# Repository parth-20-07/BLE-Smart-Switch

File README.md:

<!-- omit from toc -->
# BLE Smart Switch

**Table of Contents**

- [Why BLE Smart Switch is needed?](#why-ble-smart-switch-is-needed)
- [Features of our Smart Switch](#features-of-our-smart-switch)
- [How to use the device](#how-to-use-the-device)
- [Schematic Design](#schematic-design)
- [PCB Design](#pcb-design)
- [Rendered Images](#rendered-images)
- [Design Details](#design-details)

# Why BLE Smart Switch is needed?

The BLE Smart Switch provides convenient control over electrical sockets through Bluetooth technology. It enables users to manage home appliances remotely, ensuring energy efficiency and enhanced home automation.

# Features of our Smart Switch

- Control up to 2 sockets remotely.
- Schedule socket activation/deactivation.
- Real-time monitoring and control through a BLE app.
- Easy-to-use interface for hassle-free operation.
- Compact and modern design, suitable for various environments.

# How to use the device

1. Connect the device to the sockets you wish to control.
2. Pair the device with the BLE app.
3. Use the app to set schedules or control sockets manually.

# Schematic Design

# PCB Design

**Top View**

**Bottom View**

# Rendered Images

# Design Details

- Designed for: Ecologic Private Ltd.
- Designed by: [Parth Patel](mailto:parth.pmech@gmail.com)

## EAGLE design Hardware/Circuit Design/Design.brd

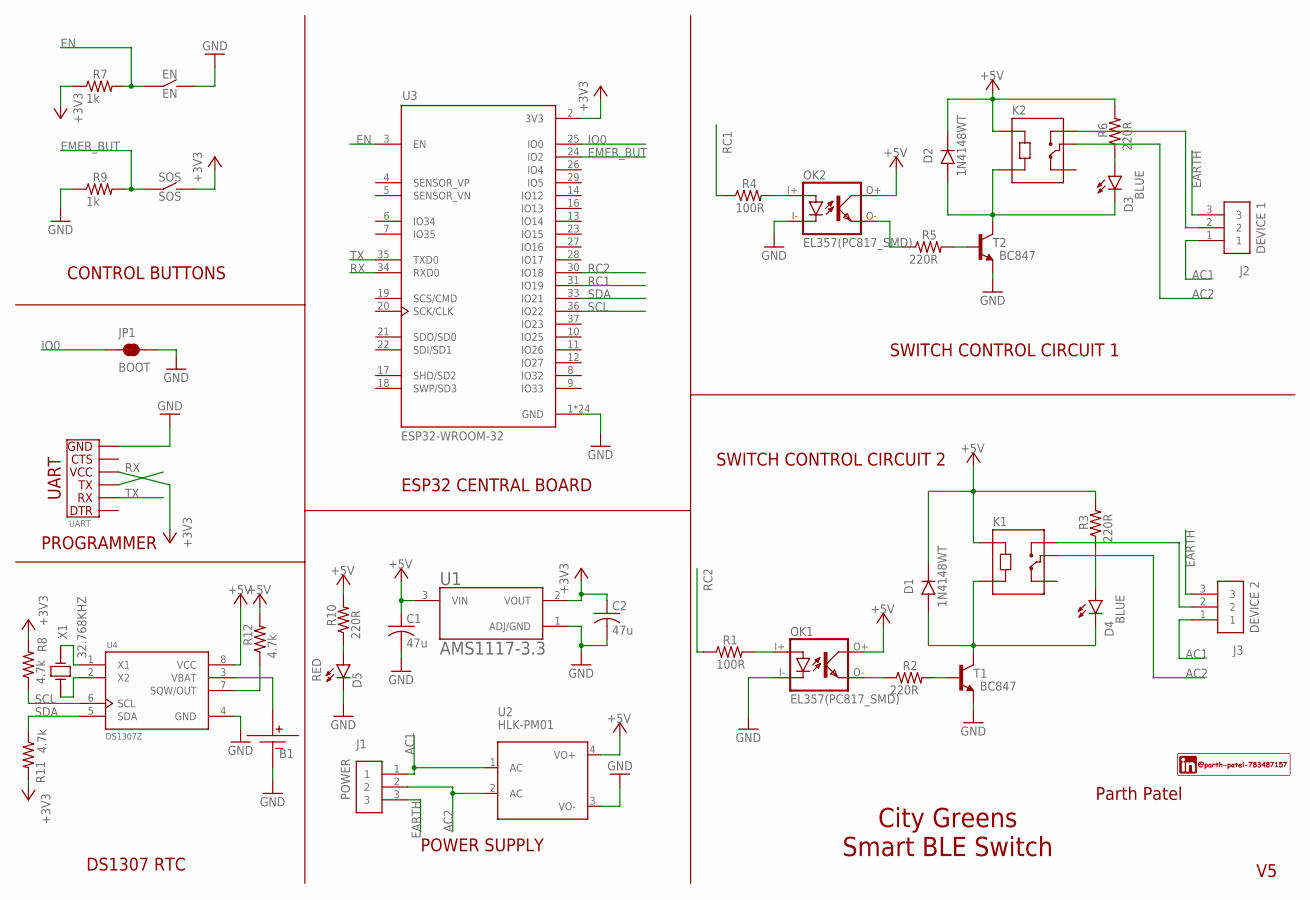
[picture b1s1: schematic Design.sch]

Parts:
B1: CR3032-METAL; CR2032-METAL
C1, C2: 47u; C0805
D1, D2: 1N4148WT; SODFL1608X70N
D3, D4: BLUE; CHIP-LED0603
D5: RED; CHIP-LED0603
EN: EN; SMD-4.5X4.5-TACTILE-PUSH-BUTTON
J1: POWER; TERMINALBLOCK_PLUGGABLE-3-7.62MM
J2: DEVICE 1; TERMINALBLOCK_PLUGGABLE-3-7.62MM
J3: DEVICE 2; TERMINALBLOCK_PLUGGABLE-3-7.62MM
JP1: BOOT; SMT-JUMPER_2_NC_TRACE_SILK
K1, K2: SRD-05VDC-SL-C; RELAY_SRD-05VDC-SL-C
OK1, OK2: EL357(PC817_SMD); SOP254P715X240-4N
R1, R4: 100R; R0805
R2, R3, R5, R6, R10: 220R; R0805
R7, R9: 1k; R0805
R8, R11, R12: 4.7k; R0805
SOS: SOS; SMD-4.5X4.5-TACTILE-PUSH-BUTTON
T1, T2: BC847; SOT23
U1: AMS1117-3.3; SOT229P700X180-4N
U2: HLK-PM01
U3: ESP32-WROOM-32; MODULE_ESP32-WROOM-32
U4: DS1307Z; SOIC127P600X175-8N
UART: UART
X1: 32.768KHZ; XTAL_AB38T-32.768KHZ

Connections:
+3V3: C2.1, R7.1, R8.2, R11.2, SOS.2.1 (S2), SOS.2.2 (S2), U1.2 (VOUT), U3.2 (3V3), UART.VCC
+5V: C1.1, D1.D+, D2.D+, K1.A1, K2.A1, OK1.O+, OK2.O+, R3.2, R6.2, R10.2, R12.2, U1.3 (VIN), U2.4 (VO+), U4.8 (VCC)
AC1: J1.1, J2.1, J3.1, U2.1 (AC)
AC2: J1.2, K1.COM, K2.COM, U2.2 (AC)
EARTH: J1.3, J2.3, J3.3
EMER_BUT: R9.2, SOS.1.1 (S1), SOS.1.2 (S1), U3.24 (IO2)
EN: EN.1.1 (S1), EN.1.2 (S1), R7.2, U3.3 (EN)
GND: B1.-VE1 (-VE), B1.-VE2 (-VE), C1.2, C2.2, D5.C, EN.2.1 (S2), EN.2.2 (S2), JP1.2, OK1.I-, OK2.I-, R9.1, T1.2 (E), T2.2 (E), U1.1 (ADJ/GND), U2.3 (VO-), U3.1 (GND), U3.15 (GND), U3.38 (GND), U3.39_1 (GND), U3.39_2 (GND), U3.39_3 (GND), U3.39_4 (GND), U3.39_5 (GND), U3.39_6 (GND), U3.39_7 (GND), U3.39_8 (GND), U3.39_9 (GND), U3.39_10 (GND), U3.39_11 (GND), U3.39_12 (GND), U3.39_13 (GND), U3.39_14 (GND), U3.39_15 (GND), U3.39_16 (GND), U3.39_17 (GND), U3.39_18 (GND), U3.39_19 (GND), U3.39_20 (GND), U3.39_21 (GND), U4.4 (GND), UART.GND
IO0: JP1.1, U3.25 (IO0)
unnamed: B1.+VE, U4.3 (VBAT)
unnamed: OK1.O-, R2.1
unnamed: OK1.I+, R1.2
unnamed: R2.2, T1.1 (B)
unnamed: R12.1, U4.7 (SQW/OUT)
unnamed: D1.D-, D4.C, K1.A2, T1.3 (C)
unnamed: D4.A, R3.1
unnamed: J3.2, K1.NO
unnamed: OK2.I+, R4.2
unnamed: OK2.O-, R5.1
unnamed: R5.2, T2.1 (B)
unnamed: D2.D-, D3.C, K2.A2, T2.3 (C)
unnamed: D3.A, R6.1
unnamed: U4.2 (X2), X1.1
unnamed: J2.2, K2.NO
unnamed: U4.1 (X1), X1.2
unnamed: D5.A, R10.1
RC1: R4.1, U3.31 (IO19)
RC2: R1.1, U3.30 (IO18)
RX: U3.34 (RXD0), UART.TX
SCL: R8.1, U3.36 (IO22), U4.6 (SCL)
SDA: R11.1, U3.33 (IO21), U4.5 (SDA)
TX: U3.35 (TXD0), UART.RX

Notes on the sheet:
City Greens Smart BLE Switch
Parth Patel
ESP32 CENTRAL BOARD
DS1307 RTC
POWER SUPPLY
SWITCH CONTROL CIRCUIT 1
SWITCH CONTROL CIRCUIT 2
CONTROL BUTTONS
PROGRAMMER

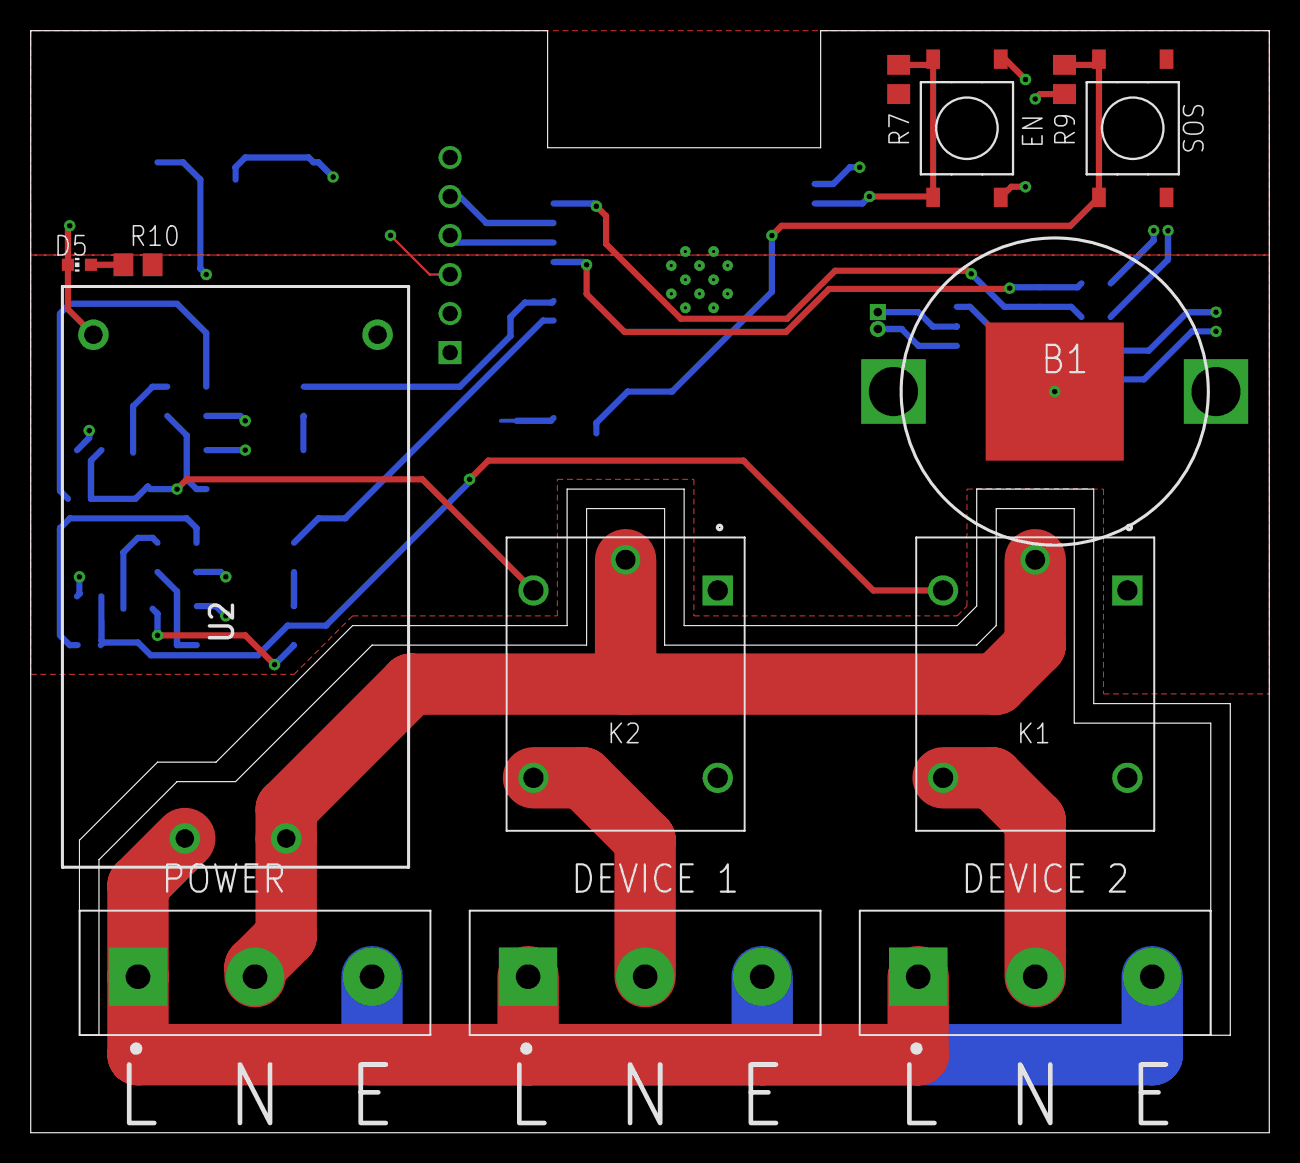
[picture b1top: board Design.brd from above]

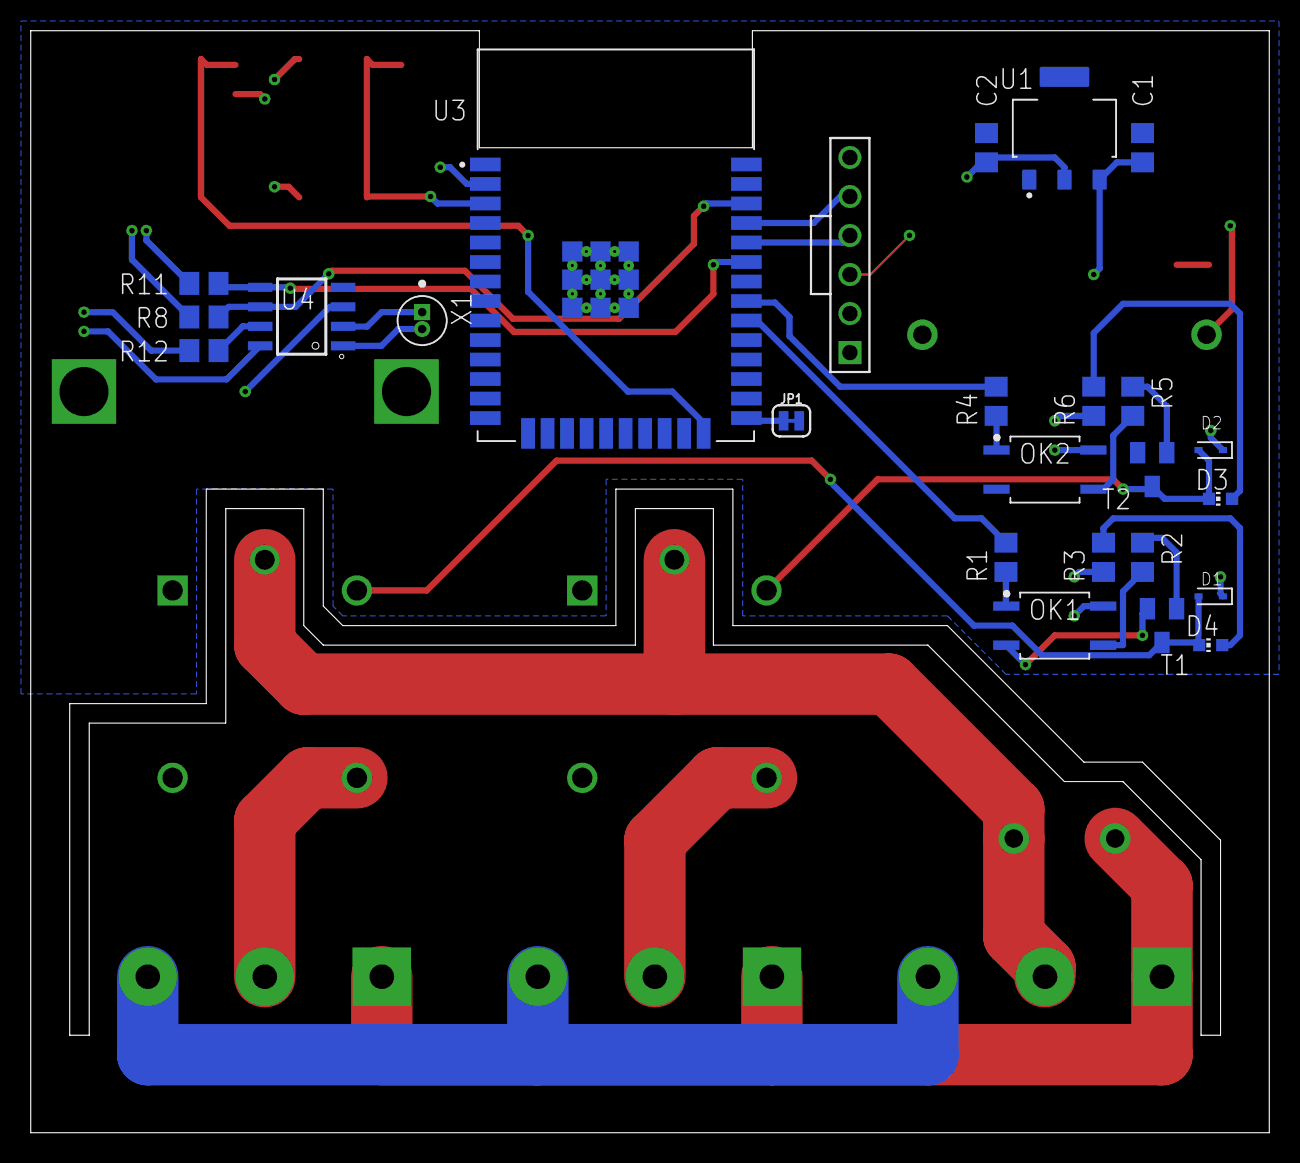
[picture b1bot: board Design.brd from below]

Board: 2 copper layers, 80.6 x 71.8 mm, 38 parts (25 on the bottom side), 32 nets.

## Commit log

2022-12-24 Add Starting Files for project

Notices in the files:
parts and their libraries:
SparkFun-Jumpers: Licensing: Creative Commons ShareAlike 4.0 International - https://creativecommons.org/licenses/by-sa/4.0
